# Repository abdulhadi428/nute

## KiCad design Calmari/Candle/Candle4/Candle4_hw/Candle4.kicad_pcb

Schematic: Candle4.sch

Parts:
ANT1: ANT_GENERAL
C1, C2, C3, C4, C12, C14, C17, C20: 0.1u
C5: 1u
C6, C8: 0.1u; CAP_0402
C7, C9: 10u; CAP_0402
C10, C11: 10pF; CAP_0402
C13, C18, C22: 220pF
C15, C16: 100pF; CAP_0402
C19, C21: 1pF; CAP_0402
C23: 1.8pF; CAP_0402
C24: 1.5pF; CAP_0402
D1: BAT54WS
DA1: NCP1400
DD1: STM32F100C4
DD2: CC2500
L1: 22uH
L2, L3, L4: 1.2nH; IND_0402
Q1: LED_RGB
R1: 30k; RES_0402
R2, R3, R4: 4k7; RES_0402
R5: 56k
R6, R7, R8: 51R; RES_0402
SW1, SW2, SW3: BUTTON
TP1, TP2: TESTPOINT
XL1: ST_SWD
XL2, XL3: CONN_1
XL4: CONN_2
XL5, XL6, XL7, XL8: CONN_3
XTAL1: 27MHz; 03225

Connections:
+3.3V: C1.1, C2.1, C3.1, C4.1, C5.1, C8.1, C9.1, C13.1, C14.1, C17.1, C18.1, C20.1, C22.1, D1.C, DA1.1 (CE), DA1.2 (OUT), DD1.1 (VBAT), DD1.9 (VDDA), DD1.24 (VDD1), DD1.36 (VDD2), DD1.48 (VDD3), DD2.4 (DVDD), DD2.9 (AVDD), DD2.11 (AVDD), DD2.14 (AVDD), DD2.15 (AVDD), DD2.18 (DGUARD), R2.2, R3.2, R4.2, XL1.1 (Vdd)
/Ant1: C15.1, DD2.12 (RF_P)
/Ant2: C16.1, DD2.13 (RF_N)
/BATT: C6.1, C7.1, L1.2, XL2.1
/BTN_DOWN: DD1.43 (PB7/SDA1/T17C1N), R3.1, SW2.2
/BTN_TX: DD1.11 (ADC1-1/T2C2/PA1), R4.1, SW3.2
/BTN_UP: DD1.42 (PB6/SCL1/T16C1N), R2.1, SW1.2
/CC_CS: DD1.13 (ADC1-3/T2C4/T15C2/RX2/PA3), DD2.7 (CSn)
/CC_GDO0: DD1.14 (ADC1-4/DAC1/CK2/PA4), DD2.6 (GDO0), TP2.1
/CC_MISO: DD1.16 (ADC1-6/T3C1/MISO1/PA6), DD2.2 (SO(GDO1))
/CC_MOSI: DD1.17 (ADC1-7/T3C2/MOSI1/PA7), DD2.20 (SI)
/CC_SCK: DD1.15 (ADC1-5/DAC2/SCK1/PA5), DD2.1 (SCLK)
/LED_B: DD1.40 ((PB4)/JTRST/(T3C1)), R8.1
/LED_G: DD1.19 (PB1/T3C4/ADC1-9), R7.1
/LED_R: DD1.18 (PB0/T3C3/ADC1-8), R6.1
/Lout: D1.A, DA1.5 (LX), L1.1
/SWCLK: DD1.37 (SWCLK/(JTCK)/(PA14)), XL1.2 (SWCLK)
/SWDIO: DD1.34 (SWDIO/(JTMS)/(PA13)), XL1.4 (SWDIO)
/WKUP: DD1.10 (ADC1-0/WKUP/PA0), R1.1, SW1.1, SW2.1, SW3.1
GND: ANT1.2 (GND), C1.2, C2.2, C3.2, C4.2, C5.2, C6.2, C7.2, C8.2, C9.2, C10.2, C11.2, C12.2, C13.2, C14.2, C17.2, C18.2, C19.2, C20.2, C22.2, C23.2, C24.2, DA1.4 (GND), DD1.8 (VSSA), DD1.23 (VSS1), DD1.35 (VSS2), DD1.44 (BOOT0), DD1.47 (VSS3), DD2.16 (GND), DD2.19 (GND), DD2.PAD (GND), L2.1, R1.2, R5.2, XL1.3 (GND), XL3.1, XL4.2 (PM), XL8.1, XL8.2 (PM), XL8.3, XTAL1.H
unnamed: C12.1, DD2.5 (DCOUPL)
unnamed: DD2.17 (RBIAS), R5.1
unnamed: DD1.30 (T1C2/TX1/PA9), XL4.1
unnamed: C21.2, C23.1, L3.1, L4.2
unnamed: Q1.BA, XL6.3
unnamed: Q1.RC, XL7.1
unnamed: Q1.BC (B), XL7.3
unnamed: Q1.GA, XL6.2 (PM)
unnamed: Q1.RA, XL6.1
unnamed: R7.2, XL5.2 (PM)
unnamed: R6.2, XL5.1
unnamed: R8.2, XL5.3
unnamed: Q1.GC (G), XL7.2 (PM)
unnamed: C16.2, C19.1, L3.2
unnamed: C15.2, C21.1, L2.2
unnamed: DD1.7 (NRST), TP1.1
unnamed: ANT1.1 (RF), C24.1, L4.1
unnamed: C11.1, DD2.10 (XOSC_Q2), XTAL1.2
unnamed: C10.1, DD2.8 (XOSC_Q1), XTAL1.1

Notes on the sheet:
Programming
Debug UART
Additional PCB
+BATTERY
-BATTERY

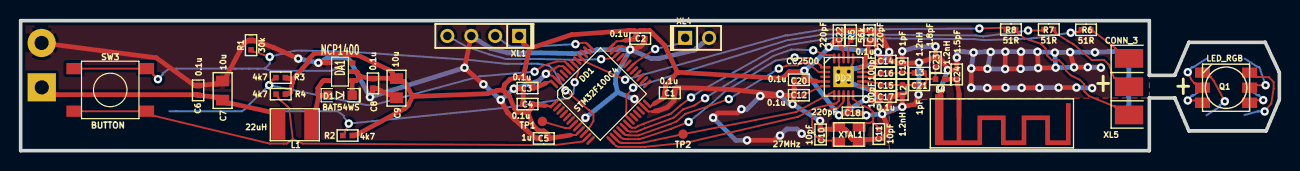
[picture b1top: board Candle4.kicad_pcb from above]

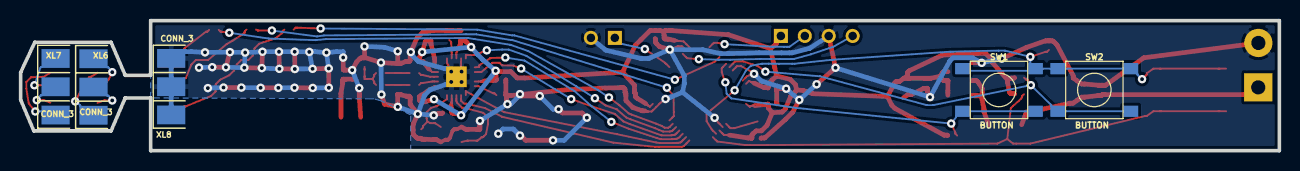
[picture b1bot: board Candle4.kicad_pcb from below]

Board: 2 copper layers, 133.6 x 13.8 mm, 56 parts (5 on the bottom side), 39 nets.

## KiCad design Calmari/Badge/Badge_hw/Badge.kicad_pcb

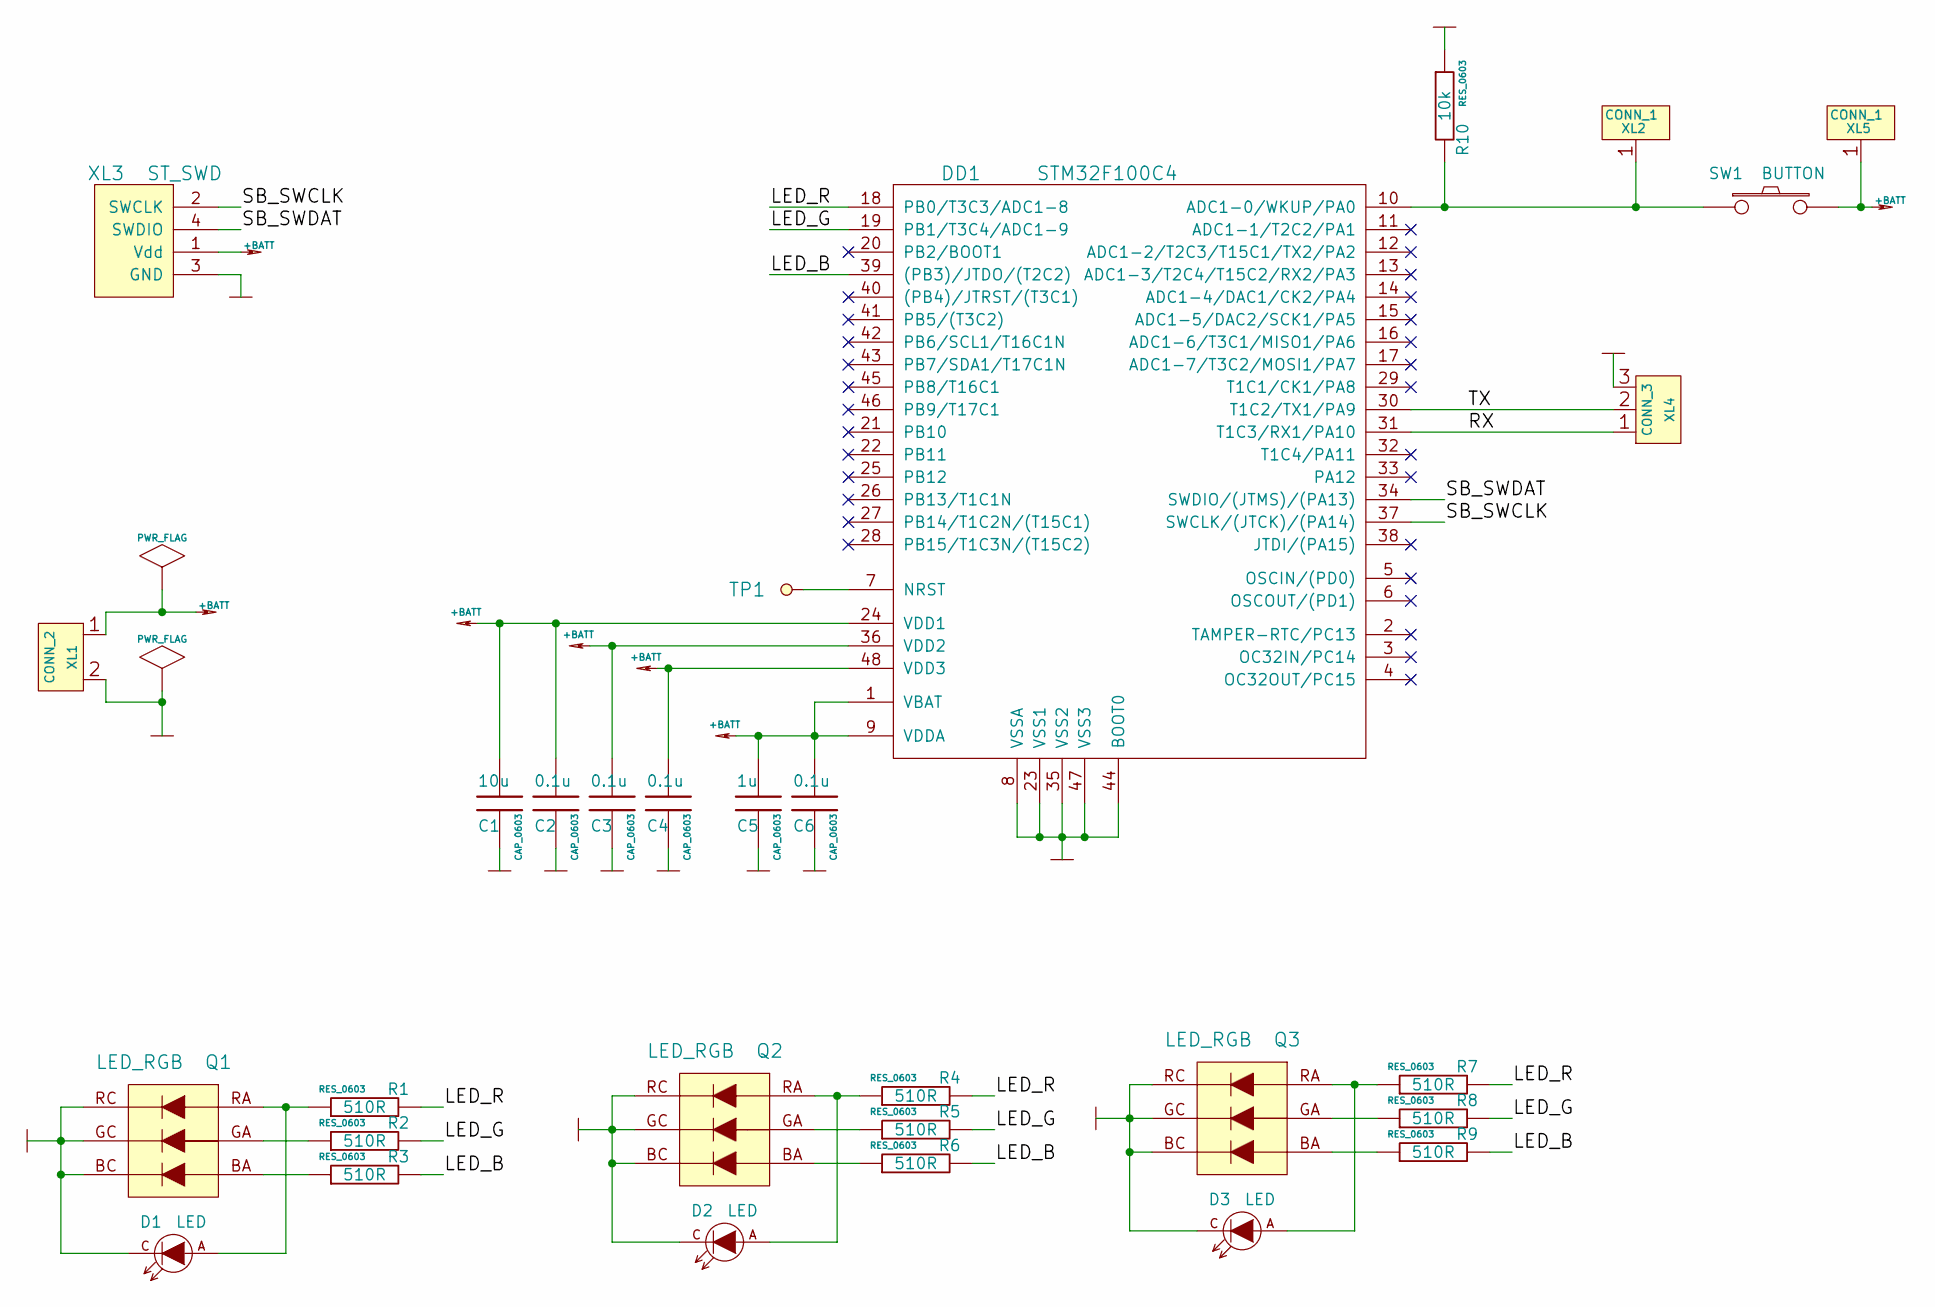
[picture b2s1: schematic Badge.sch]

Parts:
C1: 10u; CAP_0603
C2, C3, C4, C6: 0.1u; CAP_0603
C5: 1u; CAP_0603
D1, D2, D3: LED
DD1: STM32F100C4
Q1, Q2, Q3: LED_RGB
R1, R2, R3, R4, R5, R6, R7, R8, R9: 510R; RES_0603
R10: 10k; RES_0603
SW1: BUTTON
TP1: TESTPOINT
XL1: CONN_2
XL2, XL5: CONN_1
XL3: ST_SWD
XL4: CONN_3

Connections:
+BATT: C1.1, C2.1, C3.1, C4.1, C5.1, C6.1, DD1.1 (VBAT), DD1.9 (VDDA), DD1.24 (VDD1), DD1.36 (VDD2), DD1.48 (VDD3), SW1.2, XL1.1, XL3.1 (Vdd), XL5.1
/LED_B: DD1.39 ((PB3)/JTDO/(T2C2)), R3.2, R6.2, R9.2
/LED_G: DD1.19 (PB1/T3C4/ADC1-9), R2.2, R5.2, R8.2
/LED_R: DD1.18 (PB0/T3C3/ADC1-8), R1.2, R4.2, R7.2
/RX: DD1.31 (T1C3/RX1/PA10), XL4.1
/SB_SWCLK: DD1.37 (SWCLK/(JTCK)/(PA14)), XL3.2 (SWCLK)
/SB_SWDAT: DD1.34 (SWDIO/(JTMS)/(PA13)), XL3.4 (SWDIO)
/TX: DD1.30 (T1C2/TX1/PA9), XL4.2 (PM)
GND: C1.2, C2.2, C3.2, C4.2, C5.2, C6.2, D1.C, D2.C, D3.C, DD1.8 (VSSA), DD1.23 (VSS1), DD1.35 (VSS2), DD1.44 (BOOT0), DD1.47 (VSS3), Q1.BC (B), Q1.GC (G), Q1.RC, Q2.BC (B), Q2.GC (G), Q2.RC, Q3.BC (B), Q3.GC (G), Q3.RC, R10.1, XL1.2 (PM), XL3.3 (GND), XL4.3
unnamed: Q1.GA, R2.1
unnamed: Q1.BA, R3.1
unnamed: Q3.BA, R9.1
unnamed: Q2.BA, R6.1
unnamed: Q2.GA, R5.1
unnamed: D2.A, Q2.RA, R4.1
unnamed: D1.A, Q1.RA, R1.1
unnamed: D3.A, Q3.RA, R7.1
unnamed: Q3.GA, R8.1
unnamed: DD1.7 (NRST), TP1.1
unnamed: DD1.10 (ADC1-0/WKUP/PA0), R10.2, SW1.1, XL2.1

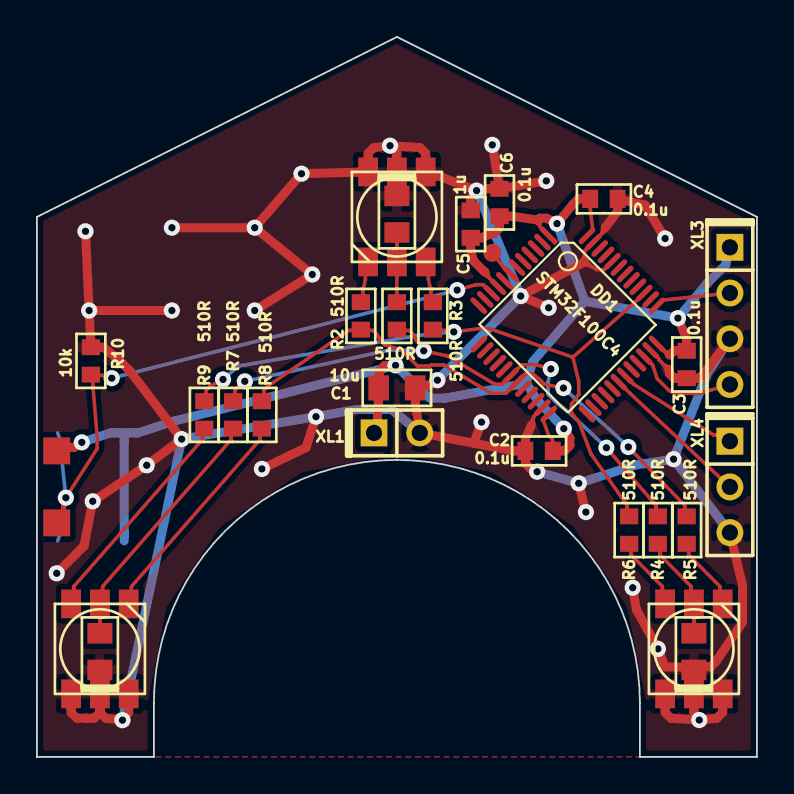
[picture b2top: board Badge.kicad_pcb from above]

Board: 2 copper layers, 40.0 x 40.0 mm, 30 parts (1 on the bottom side), 20 nets.

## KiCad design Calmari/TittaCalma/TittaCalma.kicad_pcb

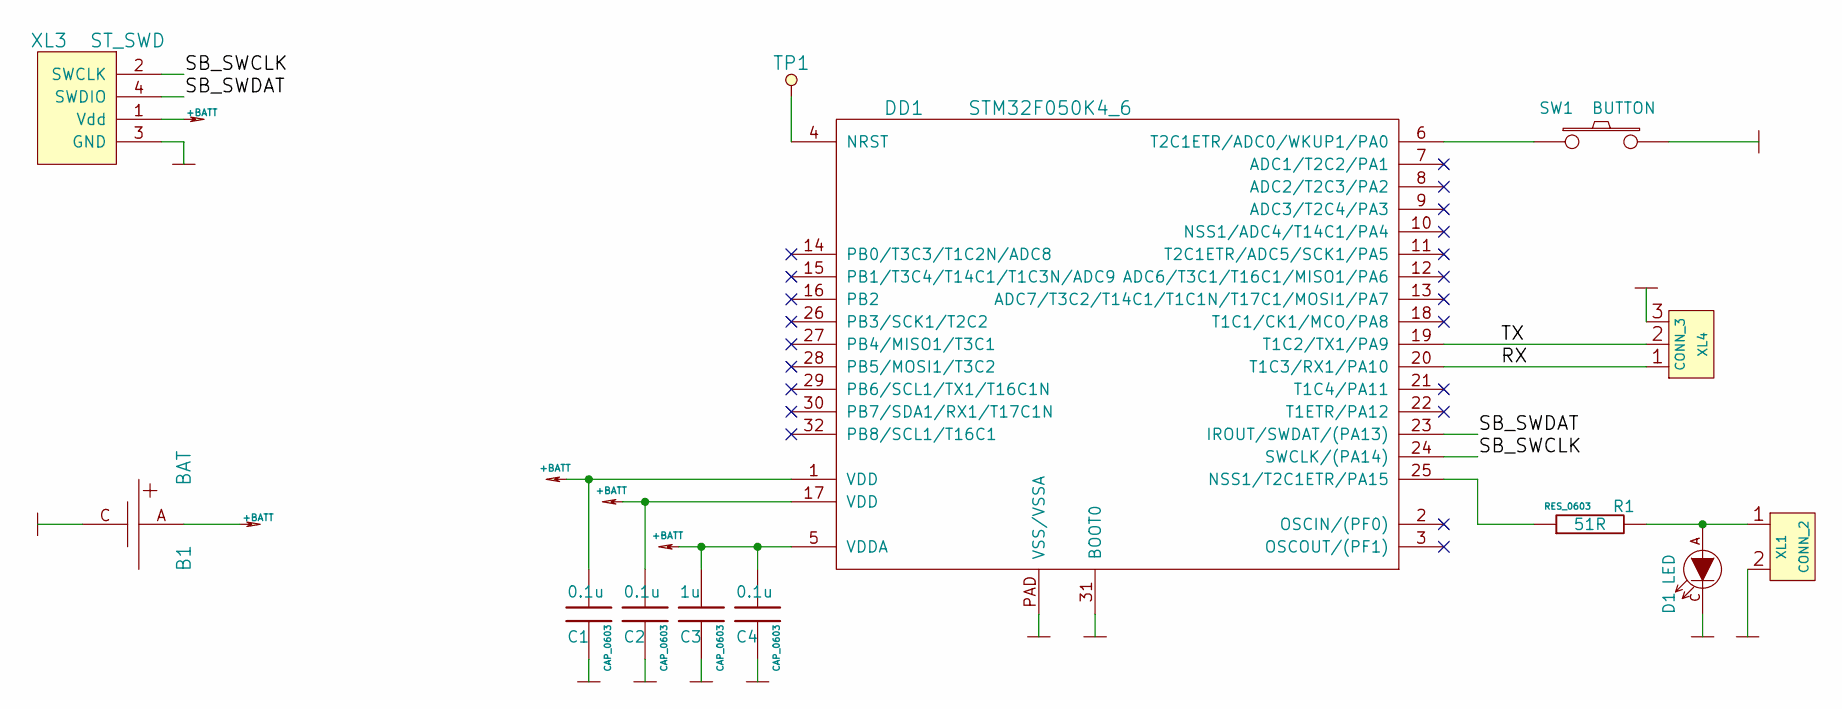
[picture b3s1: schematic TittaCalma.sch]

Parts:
B1: BAT
C1, C2, C4: 0.1u; CAP_0603
C3: 1u; CAP_0603
D1: LED
DD1: STM32F050K4_6
R1: 51R; RES_0603
SW1: BUTTON
TP1: TESTPOINT
XL1: CONN_2
XL3: ST_SWD
XL4: CONN_3

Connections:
+BATT: B1.A, C1.1, C2.1, C3.1, C4.1, DD1.1 (VDD), DD1.5 (VDDA), DD1.17 (VDD), XL3.1 (Vdd)
/RX: DD1.20 (T1C3/RX1/PA10), XL4.1
/SB_SWCLK: DD1.24 (SWCLK/(PA14)), XL3.2 (SWCLK)
/SB_SWDAT: DD1.23 (IROUT/SWDAT/(PA13)), XL3.4 (SWDIO)
/TX: DD1.19 (T1C2/TX1/PA9), XL4.2 (PM)
GND: B1.C, C1.2, C2.2, C3.2, C4.2, D1.C, DD1.31 (BOOT0), DD1.PAD (VSS/VSSA), SW1.2, XL1.2 (PM), XL3.3 (GND), XL4.3
unnamed: D1.A, R1.2, XL1.1
unnamed: DD1.6 (T2C1ETR/ADC0/WKUP1/PA0), SW1.1
unnamed: DD1.25 (NSS1/T2C1ETR/PA15), R1.1
unnamed: DD1.4 (NRST), TP1.1

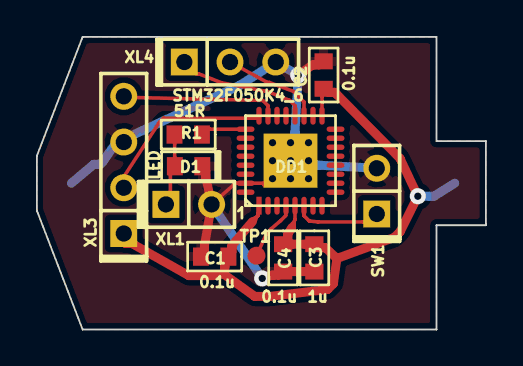
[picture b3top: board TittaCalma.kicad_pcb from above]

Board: 2 copper layers, 24.9 x 16.3 mm, 13 parts (1 on the bottom side), 10 nets.

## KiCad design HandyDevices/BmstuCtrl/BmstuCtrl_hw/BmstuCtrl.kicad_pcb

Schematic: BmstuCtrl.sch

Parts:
C1: 10u; CAP_0805
C2, C3, C5, C9, C10, C11, C12: 0.1u; CAP_0603
C4, C7, C8: 1u; CAP_0603
C6: 10n; CAP_0603
C13: 0.1u
D1, D2, D3, D4, D5: LED
D6, D7: BAT54SW
DA1: NCP583SQ
DA2: ADM3485
DA3, DA4, DA5, DA6: MC74VHC1
DD1: STM32L151CXTX
F1, F2: FUSE0R
HOLE1, HOLE2, HOLE3, HOLE4, HOLE5, HOLE6, HOLE7, HOLE9, HOLE10, HOLE11, HOLE12, HOLE13, HOLE14: HOLE_METALLED
R1: 100R; RES_0603
R2, R3, R4, R5: 1k; RES_0603
R6: 10k
R7: 10k; RES_0603
R8: 150R; RES_0603
U1: DLW21SN900SQ2
XL1: CONN_3
XL2: ST_SWD
XL3: CONN_4
XL4: CONN_3
XL5, XL6, XL7, XL8, XL10, XL11, XL12, XL13, XL14, XL15, XL16, XL17, XL18, XL19, XL20, XL21, XL22, XL23, XL24, XL25, XL26, XL27, XL28, XL29, XL30, XL31: CONN_GOST_1
XL9: DB9

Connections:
+3.3V: C1.1, C2.1, C3.1, C5.1, C6.1, C7.1, C8.1, C13.1, D6.2, D7.2, DA1.3 (Vout), DA2.8, DD1.1, DD1.9, DD1.24, DD1.36, DD1.48, XL2.1 (Vdd)
+5V: C4.1, C9.1, C10.1, C11.1, C12.1, DA1.1 (EN), DA1.4 (Vin), DA3.5 (Vcc), DA4.5 (Vcc), DA5.5 (Vcc), DA6.5 (Vcc), R7.1, XL7.1, XL10.1, XL15.1
/A: DA2.6, F1.2, U1.4
/B: DA2.7, F2.2, U1.1
/OutputEn: DA3.1 (~OE), DA4.1 (~OE), DA5.1 (~OE), DA6.1 (~OE), DD1.39, R7.2
/PATH2_1: DA3.4 (OutY), XL18.1
/PATH2_1_IN: DA3.2 (InA), DD1.40, R2.1
/PATH2_2: DA5.4 (OutY), XL26.1
/PATH2_2_IN: DA5.2 (InA), DD1.42, R4.1
/PATH3_1: DA4.4 (OutY), XL20.1
/PATH3_1_IN: DA4.2 (InA), DD1.41, R3.1
/PATH3_2: DA6.4 (OutY), XL28.1
/PATH3_2_IN: DA6.2 (InA), DD1.43, R5.1
/PWR_24V: XL5.1, XL16.1, XL24.1
/RS485_A: D6.3, F1.1, R8.1, U1.3, XL9.1
/RS485_B: D7.3, F2.1, R8.2, U1.2, XL9.2
/RX_I_TX_K: DD1.21, XL12.1
/SWCLK: DD1.37, XL2.2 (SWCLK)
/SWDIO: DD1.34, XL2.4 (SWDIO)
/TX_I_RX_K: DD1.22, XL13.1
/Tx_Rx: DA2.2, DA2.3, DD1.14, R6.1, XL4.2 (PM)
/UART2_RX: DA2.1, DD1.13, XL4.3
/UART2_TX: DA2.4, DD1.12, XL4.1
/UART_RX: DD1.31, XL1.3
/UART_TX: DD1.30, XL1.2 (PM)
GND: C1.2, C2.2, C3.2, C4.2, C5.2, C6.2, C7.2, C8.2, C9.2, C10.2, C11.2, C12.2, C13.2, D1.C, D2.C, D3.C, D4.C, D5.C, D6.1, D7.1, DA1.2 (GND), DA2.5, DA3.3 (GND), DA4.3 (GND), DA5.3 (GND), DA6.3 (GND), DD1.8, DD1.23, DD1.35, DD1.44, DD1.47, HOLE1.Hle, HOLE2.Hle, HOLE3.Hle, HOLE4.Hle, HOLE5.Hle, HOLE6.Hle, HOLE7.Hle, HOLE9.Hle, HOLE10.Hle, HOLE11.Hle, HOLE12.Hle, HOLE13.Hle, HOLE14.Hle, R6.2, XL1.1, XL2.3 (GND), XL3.4, XL6.1, XL8.1, XL9.5, XL9.H (SHLD), XL11.1, XL14.1, XL22.1, XL30.1
unnamed: DD1.2, XL3.3
unnamed: DD1.3, XL3.2 (PM)
unnamed: DD1.4, XL3.1
unnamed: DD1.18, R1.2
unnamed: D1.A, R1.1
unnamed: D4.A, R4.2
unnamed: D3.A, R3.2
unnamed: D5.A, R5.2
unnamed: D2.A, R2.2

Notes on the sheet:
Debug port
Programming
CPU
Power
Just Pins
3.3V 150mA power regulator
Shottki supress positive and negative peaks at signal fronts
Disable TX when start
RS-485
Imitator
Power input
To LNA
IND_COMM
IND2
IND3
Open_ALL_Paths
Switch1
Switch2
Output buffers Disabled by default
Holes
RS-485 interface
Power & Signal Connectors

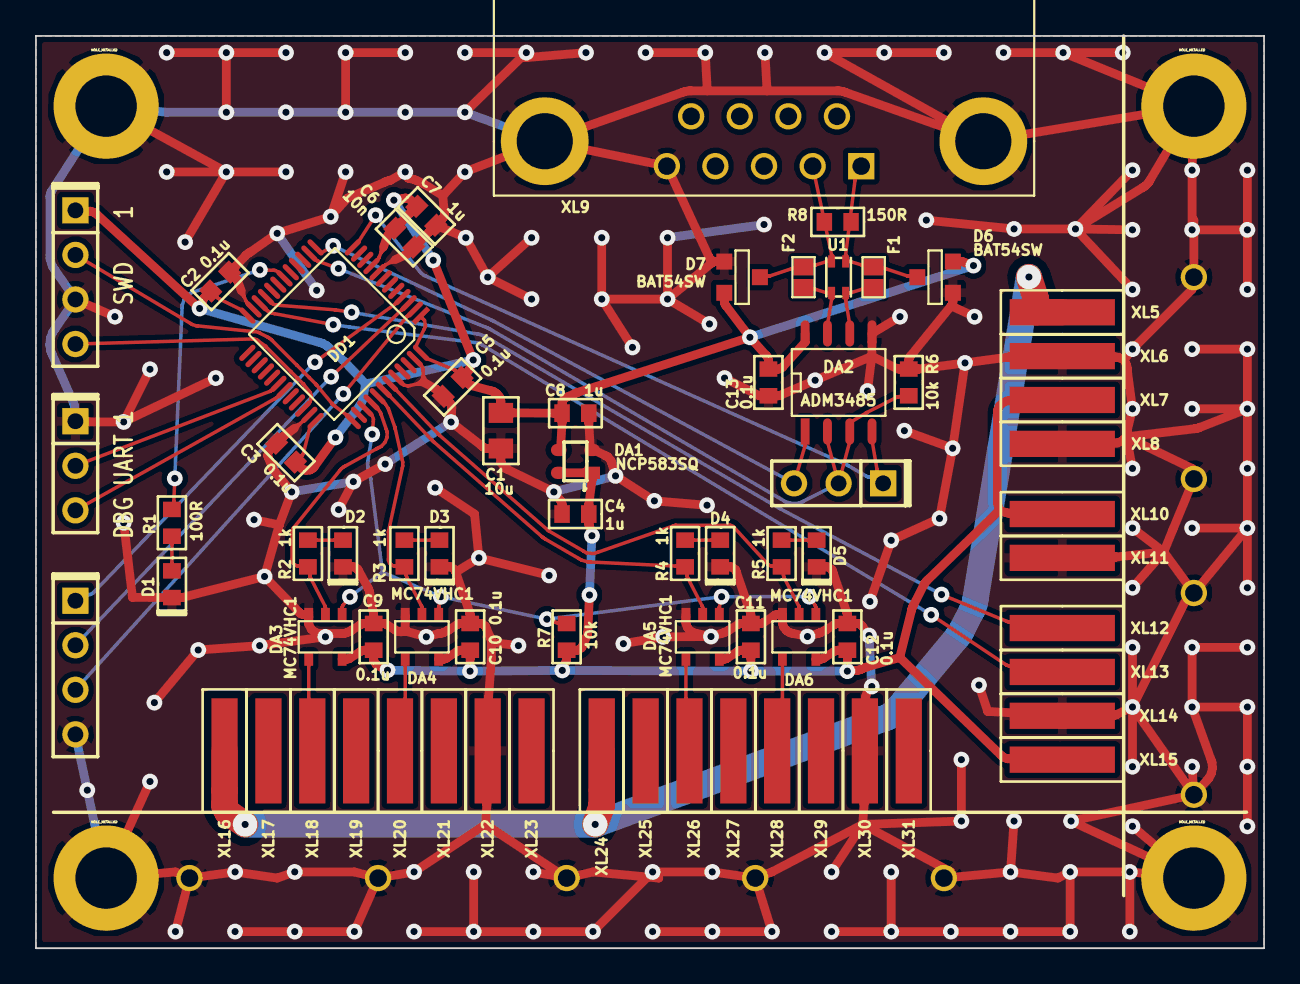
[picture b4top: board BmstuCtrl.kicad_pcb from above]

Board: 2 copper layers, 70.0 x 52.0 mm, 82 parts (0 on the bottom side), 35 nets.

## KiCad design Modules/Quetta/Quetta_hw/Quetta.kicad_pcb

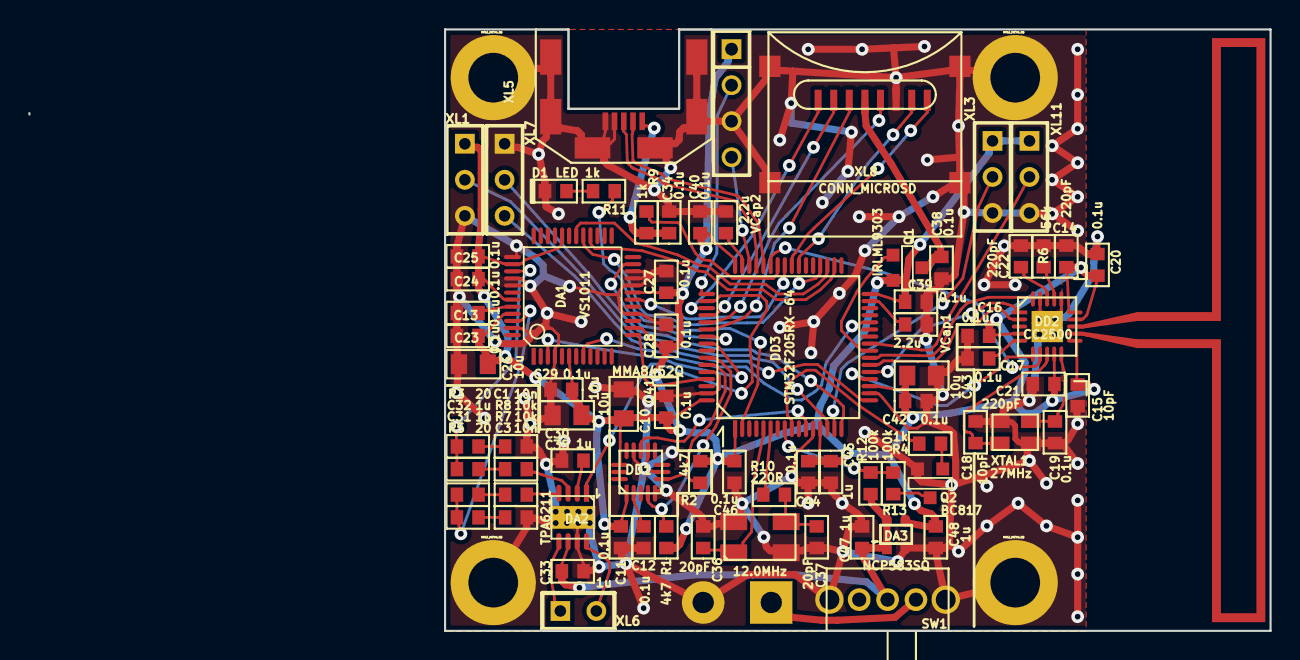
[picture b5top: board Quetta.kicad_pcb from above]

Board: 2 copper layers, 58.2 x 42.4 mm, 83 parts (0 on the bottom side), 71 nets.

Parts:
ANT1: ANT_PCB_NOCNTR; ANT_FOLDED_DIPOLE2
C1, C3: 10n; CAP_0603
C10, C26, C30, C43: 10u; CAP_0805
C11, C12, C13, C15, C16, C17, C20, C23, C24, C25, C27, C28, C29, C34, C38, C39, C40, C41, C42, C44, C46: 0.1u; CAP_0603
C14, C21, C22: 220pF; CAP_0603
C18, C19: 10pF; CAP_0603
C31, C32, C33, C35, C45, C47, C48: 1u; CAP_0603
C36, C37: 20pF; CAP_0603
D1: LED; LED0603
DA1: VS1011; LQFP48
DA2: TPA6211; DRB8
DA3: NCP583SQ; SC82AB
DD1: MMA8452Q; QFN16_5_3
DD2: CC2500; QFN20
DD3: STM32F205RX-64; LQFP64
HOLE1, HOLE2, HOLE3, HOLE4: HOLE_METALLED; Hole3_5_out6mm
Q1: IRLML9303; SOT23
Q2: BC817; SOT23
R1, R2: 4k7; RES_0603
R3, R5: 20; RES_0603
R4, R9, R11: 1k; RES_0603
R6: 56k; RES_0603
R7, R8: 10k; RES_0603
R10: 220R; RES_0603
R12, R13: 100k; RES_0603
SW1: SWITCH_H; SW_SK12D07VG
VCap1, VCap2: 2.2u; CAP_0603
XL1, XL3, XL7, XL11: CONN_3; SIL-3
XL4: ST_SWD; SIL-4
XL5: USB_MICRO_B; USBmicro_MOLEX_WM17142
XL6: CONN_2; SIL-2
XL8: CONN_MICROSD; MICROSD_CAP_FIX05A
XL9: CONN_1; SIL1_SQUARE_1MM5
XL10: CONN_1; SIL1_ROUND_1MM5
XTAL1: 27MHz; CRYSTAL_03225C4
XTAL2: 12.0MHz; CRYSTAL_0503x4-4

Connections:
+3.3V: C10.1, C11.1, C14.1, C15.1, C16.1, C20.1, C21.1, C23.1, C24.1, C25.1, C26.1, C27.1, C28.1, C29.1, C30.1, C39.1, C40.1, C41.1, C42.1, C43.1, C44.1, C45.1, C46.1, C48.1, DA1.6, DA1.14, DA1.19, DA1.32, DA1.38, DA1.43, DA1.45, DA3.3, DD1.1, DD1.14, DD2.4, DD2.9, DD2.11, DD2.14, DD2.15, DD3.1, DD3.13, DD3.19, DD3.32, DD3.48, DD3.64, Q1.2, R1.1, R2.2, XL1.1, XL3.1, XL4.1, XL11.1
+5V: C34.1, R9.2, XL5.1
+BATT: C33.1, C47.1, DA2.6, DA3.1, DA3.4, R12.1, SW1.2
/12MHz_Clk: DA1.18, DD3.41
/ACC_IRQ: DD1.11, DD3.11
/AMPLF_SHDN: DA2.1, DD3.50
/Ant1: ANT1.1, DD2.12
/Ant2: ANT1.2, DD2.13
/BATTERY_PLUS: SW1.3, XL9.1
/BAT_MEASURE: DD3.9, R4.1
/CC_CS: DD2.7, DD3.43
/CC_GDO0: DD2.6, DD3.20
/CC_MISO: DD2.2, DD3.22
/CC_MOSI: DD2.20, DD3.23
/CC_SCK: DD2.1, DD3.21
/I2C_SCL: DD1.4, DD3.58, R1.2
/I2C_SDA: DD1.6, DD3.59, R2.1
/RX2: DD3.17, XL7.3
/SD_CLK: DD3.53, XL8.5
/SD_CMD: DD3.54, XL8.3
/SD_DAT0: DD3.39, XL8.7
/SD_DAT1: DD3.40, XL8.8
/SD_DAT2: DD3.51, XL8.1
/SD_DAT3: DD3.52, XL8.2
/SD_POWER: DD3.24, Q1.1
/SD_VDD: C38.1, Q1.3, XL8.4
/SND_L: C31.2, DA1.46, R5.2
/SND_R: C32.2, DA1.39, R3.2
/SNS1_OUT: DD3.14, XL1.2
/SNS2_OUT: DD3.15, XL3.2
/SNS3_OUT: DD3.25, XL11.2
/SWCLK: DD3.49, XL4.2
/SWDIO: DD3.46, XL4.4
/TX2: DD3.16, XL7.2
/UBat_2: DD3.8, R12.2, R13.1
/USB_DM: DD3.44, XL5.2
/USB_DP: DD3.45, XL5.3
/VS_DREQ: DA1.8, DD3.28
/VS_RST: DA1.3, DD3.56
/VS_SCLK: DA1.28, DD3.34
/VS_SI: DA1.29, DD3.36
/VS_SO: DA1.30, DD3.35
/VS_XCS: DA1.23, DD3.55
/VS_XDCS: DA1.13, DD3.61
GND: C1.1, C3.1, C10.2, C11.2, C12.2, C13.2, C14.2, C15.2, C16.2, C17.2, C18.2, C19.2, C20.2, C21.2, C22.2, C23.2, C24.2, C25.2, C26.2, C27.2, C28.2, C29.2, C30.2, C33.2, C34.2, C35.2, C36.2, C37.2, C38.2, C39.2, C40.2, C41.2, C42.2, C43.2, C44.2, C45.2, C46.2, C47.2, C48.2, D1.C, DA1.4, DA1.16, DA1.20, DA1.21, DA1.22, DA1.37, DA1.40, DA1.41, DA1.47, DA2.7, DA2.PAD, DA3.2, DD1.5, DD1.7, DD1.10, DD1.12, DD2.16, DD2.19, DD2.PAD, DD3.12, DD3.18, DD3.60, DD3.63, HOLE1.Hle, HOLE2.Hle, HOLE3.Hle, HOLE4.Hle, Q2.2, R6.2, SW1.H, VCap1.2, VCap2.2, XL1.3, XL3.3, XL4.3, XL5.4, XL5.5, XL5.SHLD, XL7.1, XL8.6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
unnamed: C12.1, DD1.2
unnamed: DD3.47, VCap2.1
unnamed: C13.1, DA1.44
unnamed: DD2.17, R6.1
unnamed: C17.1, DD2.5
unnamed: C22.1, DD2.18
unnamed: C18.1, DD2.8, XTAL1.1
unnamed: C19.1, DD2.10, XTAL1.2
unnamed: C37.1, R10.2, XTAL2.2
unnamed: DD3.6, R10.1
unnamed: Q2.3, R13.2
unnamed: Q2.1, R4.2
unnamed: DD3.42, R9.1
unnamed: C32.1, R8.1
unnamed: DA2.4, R7.2
unnamed: DA2.8, XL6.2
unnamed: DA2.5, XL6.1
unnamed: DD3.31, VCap1.1
unnamed: DD3.2, R11.1
unnamed: C1.2, R3.1
unnamed: C3.2, R5.1
unnamed: C36.1, DD3.5, XTAL2.1
unnamed: C31.1, R7.1
unnamed: DA2.3, R8.2
unnamed: C35.1, DA2.2
unnamed: D1.A, R11.2

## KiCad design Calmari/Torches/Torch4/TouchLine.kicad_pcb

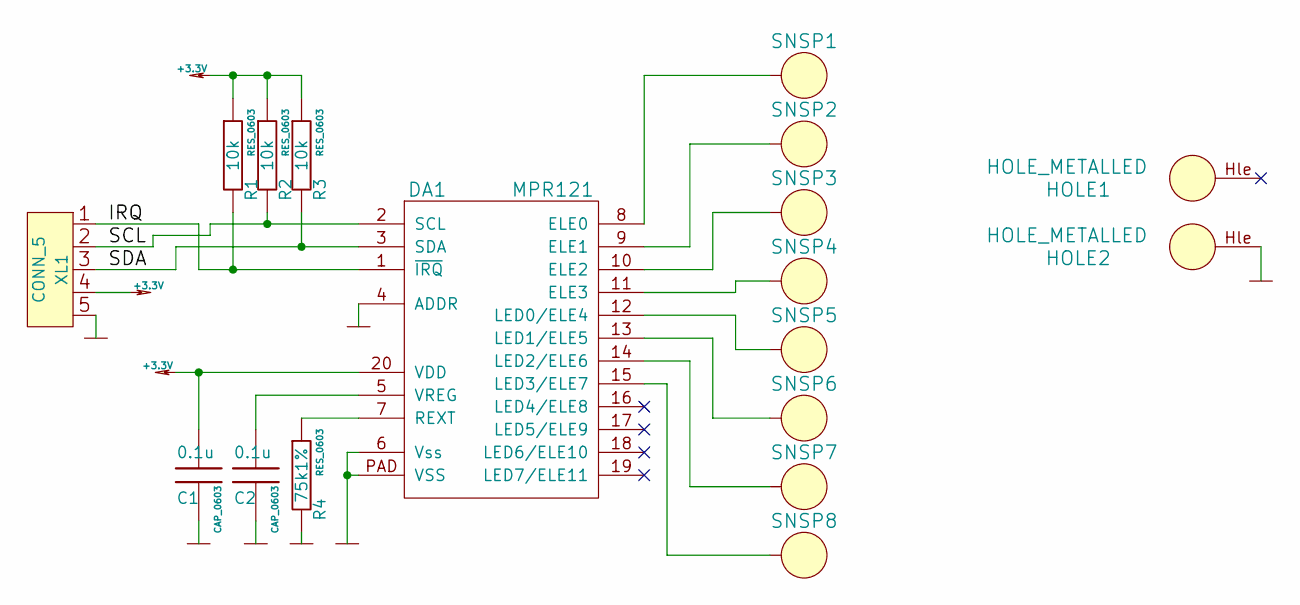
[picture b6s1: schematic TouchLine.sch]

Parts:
C1, C2: 0.1u; CAP_0603
DA1: MPR121
HOLE1, HOLE2: HOLE_METALLED
R1, R2, R3: 10k; RES_0603
R4: 75k1%; RES_0603
SNSP1, SNSP2, SNSP3, SNSP4, SNSP5, SNSP6, SNSP7, SNSP8: SENSORPAD
XL1: CONN_5

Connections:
+3.3V: C1.1, DA1.20 (VDD), R1.1, R2.1, R3.1, XL1.4
/IRQ: DA1.1 (~IRQ), R1.2, XL1.1
/SCL: DA1.2 (SCL), R2.2, XL1.2
/SDA: DA1.3 (SDA), R3.2, XL1.3
GND: C1.2, C2.2, DA1.4 (ADDR), DA1.6 (Vss), DA1.PAD (VSS), HOLE2.Hle, R4.2, XL1.5
unnamed: DA1.11 (ELE3), SNSP4.1
unnamed: DA1.12 (LED0/ELE4), SNSP5.1
unnamed: DA1.13 (LED1/ELE5), SNSP6.1
unnamed: DA1.14 (LED2/ELE6), SNSP7.1
unnamed: DA1.7 (REXT), R4.1
unnamed: C2.1, DA1.5 (VREG)
unnamed: DA1.9 (ELE1), SNSP2.1
unnamed: DA1.15 (LED3/ELE7), SNSP8.1
unnamed: DA1.10 (ELE2), SNSP3.1
unnamed: DA1.8 (ELE0), SNSP1.1

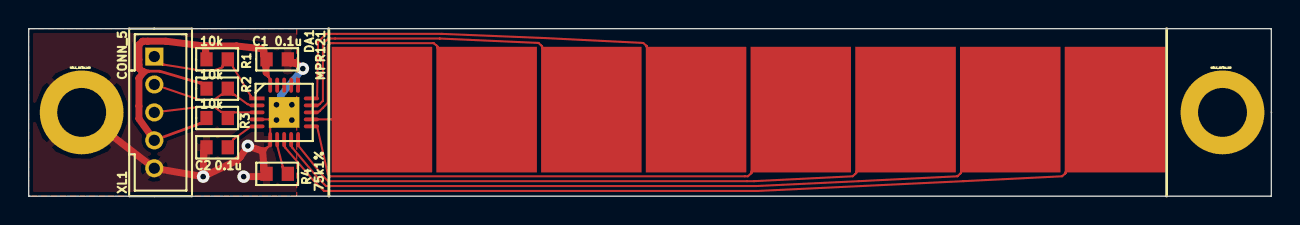
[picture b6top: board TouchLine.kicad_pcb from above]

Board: 2 copper layers, 89.0 x 12.0 mm, 18 parts (0 on the bottom side), 15 nets.

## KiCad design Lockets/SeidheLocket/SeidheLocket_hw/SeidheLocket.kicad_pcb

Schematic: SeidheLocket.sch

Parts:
ANT1: ANT_PCB_MONO
B3: BAT
BLN1: 0896BM15A0001
C1, C12: 10u; CAP_0603
C2: 1.8pF
C3, C8: 220pF
C4, C6: 10n
C5: 3.3pF
C7, C11, C21, C23: 0.1u
C9, C10: 10pF; CAP_0402
C13, C14, C18: 0.1u; CAP_0402
C15: 10n; CAP_0402
C16: 1u; CAP_0402
C22, C24: 10u
D1, D2: BAT54WS
DA1: NCP1400
DD1: STM32L151CXTX
DD2: CC1101
L1: 5.6nH; IND_0402
L2: 22uH
M1: MOTOR_PAD
Q1: MMBT2222
Q2: LED_RGB 5050
R1: 1k; RES_0402
R2: 56k
R3, R4, R5: 51R; RES_0603
R12: 1k
RP1, RP2: REFPOINT
SW1: BUTTON
TP1, TP2: TESTPOINT
XL1: ST_SWD
XL2: CONN_3
XL3: CONN_4
XTAL1: 27MHz; 03225

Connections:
+3.3V: C3.1, C4.1, C5.1, C6.1, C7.1, C8.1, C12.1, C13.1, C14.1, C15.1, C16.1, C18.1, C23.1, C24.1, D2.C, DA1.1 (CE), DA1.2 (OUT), DD1.1, DD1.9, DD1.24, DD1.36, DD1.48, DD2.4 (DVDD), DD2.9 (AVDD), DD2.11 (AVDD), DD2.14 (AVDD), DD2.15 (AVDD), DD2.18 (DGUARD), XL1.1 (Vdd)
+BATT: B3.A, C1.1, C21.1, C22.1, D1.C, L2.2, M1.2 (-), R1.2
/BLUE_LED: DD1.18, R5.1
/CC_CS: DD1.14, DD2.7 (CSn)
/CC_GDO0: DD1.13, DD2.6 (GDO0), TP1.1
/CC_GDO2: DD1.12, DD2.3 (GDO2), TP2.1
/CC_MISO: DD1.16, DD2.2 (SO(GDO1))
/CC_MOSI: DD1.17, DD2.20 (SI)
/CC_SCK: DD1.15, DD2.1 (SCLK)
/GREEN_LED: DD1.41, R4.1
/Lout: D2.A, DA1.5 (LX), L2.1
/RED_LED: DD1.19, R3.1
/RF1: BLN1.4 (Bal2), DD2.12 (RF_P)
/RF2: BLN1.3 (Bal1), DD2.13 (RF_N)
/SWCLK: DD1.37, XL1.2 (SWCLK)
/SWDIO: DD1.34, XL1.4 (SWDIO)
/UART_RX: DD1.31, XL2.3
/UART_TX: DD1.30, XL2.2 (PM)
/Vibro: DD1.42, R12.1
/VibroOut: D1.A, M1.1 (+), Q1.3 (C)
GND: B3.C, BLN1.2 (GND), BLN1.5 (GND), BLN1.6 (GND), C1.2, C2.2, C3.2, C4.2, C5.2, C6.2, C7.2, C8.2, C9.2, C10.2, C11.2, C12.2, C13.2, C14.2, C15.2, C16.2, C18.2, C21.2, C22.2, C23.2, C24.2, DA1.4 (GND), DD1.8, DD1.23, DD1.35, DD1.44, DD1.47, DD2.16 (GND), DD2.19 (GND), DD2.PAD (GND), M1.PAD (GND), Q1.2 (E), Q2.BC (B), Q2.GC (G), Q2.RC, R2.2, SW1.1, XL1.3 (GND), XL2.1, XL3.4, XTAL1.H
unnamed: ANT1.1, C2.1, L1.1
unnamed: DD1.22, XL3.2 (PM)
unnamed: DD1.25, XL3.3
unnamed: BLN1.1 (Unbal), L1.2
unnamed: DD1.45, SW1.2
unnamed: DD1.21, XL3.1
unnamed: DD1.10, R1.1
unnamed: DD2.17 (RBIAS), R2.1
unnamed: C11.1, DD2.5 (DCOUPL)
unnamed: Q2.BA, R5.2
unnamed: Q2.GA, R4.2
unnamed: Q2.RA, R3.2
unnamed: Q1.1 (B), R12.2
unnamed: C10.1, DD2.10 (XOSC_Q2), XTAL1.2
unnamed: C9.1, DD2.8 (XOSC_Q1), XTAL1.1

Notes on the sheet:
Debug port
Programming
CPU
Power
Radio
Matching circuit
L-07C5N6SV4
500R07S1R8BV4
1xAA
Just Pins
Indication

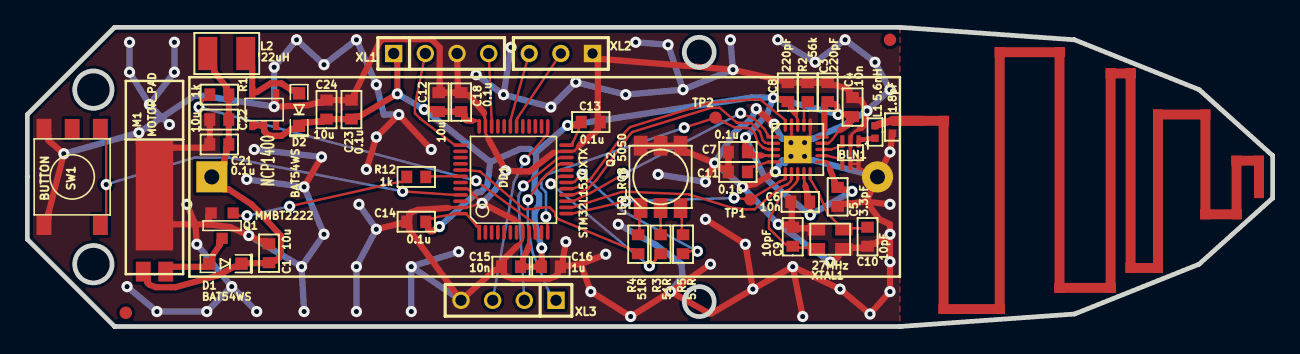
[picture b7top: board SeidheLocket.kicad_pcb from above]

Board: 2 copper layers, 99.9 x 24.0 mm, 49 parts (0 on the bottom side), 36 nets.

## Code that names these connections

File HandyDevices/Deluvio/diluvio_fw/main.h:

/*
 * File:   main.h
 * Author: Kreyl Laurelindo
 *
 * Created on 29 Íîÿáðü 2010 ã., 19:49
 */

#ifndef MAIN_H
#define	MAIN_H

#include "common.h"
#include <avr/io.h>
#include <stdbool.h>

// Power ok
#define PWROK_DDR   DDRA
#define PWROK_PORT  PORTA
#define PWROK_PIN   PINA
#define PWROK_P     PA3
#define POWER_OK()  bit_is_set(PWROK_PIN, PWROK_P)

// Pumps
#define PUMP_COUNT  4
#define PUMP_DDR    DDRA
#define PUMP_PORT   PORTA
#define PUMP1P      PA4
#define PUMP2P      PA5
#define PUMP3P      PA6
#define PUMP4P      PA7
// Max pump ON duration, s
#define PUMP_MAX_DURATION   252

// Water sensor
#define WATER_SNS_DDR    DDRA
#define WATER_SNS_PORT   PORTA
#define WATER_SNS_PIN    PINA
#define WATER_IN_P       PA1
#define WATER_R_P        PA0

#define WATER_IN_IS_HI() bit_is_set  (WATER_SNS_PIN, WATER_IN_P)
#define WATER_IN_IS_LO() bit_is_clear(WATER_SNS_PIN, WATER_IN_P)
#define WATER_R_LO()     WATER_SNS_PORT &= ~(1<<WATER_R_P)
#define WATER_R_HI()     WATER_SNS_PORT |=  (1<<WATER_R_P)

typedef enum {ModeDays, ModeHours} PumpPeriodMode_t;
typedef enum {PmpIdle, PmpMustPump, PmpBeeping, PmpPumping} PumpState_t;
typedef struct {
    bool Enabled;
    PumpPeriodMode_t PeriodMode;
    uint8_t Period;
    uint8_t PeriodLeft;
    uint8_t StartHour;
    uint8_t Duration;
    PumpState_t State;
    uint16_t Counter;
    uint8_t ID;
} pump_t;

extern pump_t Pumps[PUMP_COUNT];
extern bool IsPumping, PumpsSettingsChanged;

// ============================== Prototypes ===================================
void GeneralInit(void);

void PumpOn(uint8_t APump);
void PumpOffAll(void);
void Task_Pump(void);
void PumpsLoad(void);
void PumpsSave(void);

void CheckWater(void);
void CheckBattery(void);

void Task_Sleep(void);

#endif	/* MAIN_H */

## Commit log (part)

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2013-06-16 Event-driven, only one channel
2013-06-16 Tirusse2 release candidate
2013-06-16 Alfa-version. All features are working but some bugs are still possible
2013-06-17 Добавлена цветовая дифференциация добра и зла
2013-07-06 allow nullable controls on panel
2013-07-06 med staff
2013-07-06 minor synch
2013-07-06 minor icons
2013-07-06 OpenSpace fork
2013-07-06 DAC-based transmission works.
2013-07-07 price of honor
2013-07-07 deprecated old repositories
2013-07-07 remove
2013-07-07 exe-dll schema
2013-07-07 TF factory
2013-07-07 Timer-based generator added.
2013-07-07 move to vs10
2013-07-07 ITextStream.h
2013-07-07 TF factory 2
2013-07-08 new conv
2013-07-08 Panel factory changed
2013-07-08 removed useless trash
2013-07-10 led resistors change
2013-07-12 lume2 case added
2013-07-13 Calma04 added
2013-07-14 calma04 pcb added
2013-07-20 Candle3 btn evt processing in progress
2013-07-21 Radio works.
2013-07-23 Glove pre-revolution
2013-07-24 Angle-based measurements
2013-07-26 MINOR changes in ImageConvertor
2013-07-26 MINOR proper DllMain and generate debug info
2013-07-26 MINOR proper DllMain + tests + generate debug info
2013-07-26 MINOR merge with Krivda - updated to new ver
2013-07-26 images
2013-07-26 MINOR changes in API
2013-07-26 MINOR changes in visualizer
2013-07-26 MINOR to compile
2013-07-27 MAJOR Spec for app
2013-08-09 Indication changed, sleep allowed
2013-08-09 Demonstration of charge level at startup implemented
2013-08-10 Checked memory footprint, CPU time consumtion etc.
2013-08-12 After stats
2013-08-23 Girandole dome matrix & punch
2013-08-25 new stuff except armlet shell
2013-08-25 new krivda UI with factories, imagelists, pictureboxes
2013-08-28 Удален код настройки замков
2013-08-28 Убраны падения при невыбранном типе пилюль
2013-08-28 ShipStatus added. Including RanmaSubsystemStatus.cs
2013-08-29 Сделано сохранение и загрузка из файла кораблей
2013-08-29 PRICE OF HONOR 2 (Plan A:new UI), emulator only version in case of success will be merged with main development
2013-08-29 Перераспределены файлы по проектам, начат вопрос UI
2013-08-29 Добавлен параметр вероятности попадания
2013-08-29 Убраны остатки замеса про замки
2013-08-29 Добавлено сохранение комнат
2013-08-29 Добавлены взрывы комнат
2013-08-29 Добавил делегаты к классу корабля
2013-08-29 Удален старый UI взрыва отсеков
2013-08-29 Отображать имена отсеков в таблице
2013-08-29 Развернуть горизонтально контролы отсеков
2013-08-29 Окрасивлен GUI
2013-08-29 Добавлена функция взрыва случайного отсека и тестовая кнопка в нему.
2013-08-31 ChibiGate firmware completed.
2013-08-31 Большой update
2013-08-31 Удалил весь дублирующий код из {Lak/Big}Ship
    Теперь они отличаются ТОЛЬКО количеством плат и подсистем.
2013-08-31 Fixed bug with i2c; last byte dissapeared time after time.
2013-09-01 Проглатываем исключения при чтении пилюли
2013-09-01 Добавил таблицу значений и правильное значение для Ready
2013-09-01 Убрано сохранение кораблей и загрузка из профиля, теперь всегда грузим их из текущего каталога
2013-09-01 Дал название окну приложения
2013-09-01 Добавил IsOnline; Убрал ошибочный коммент с вопросом
2013-09-01 Теперь RanmaPlate работает поверх GateModel Статус online корабля отображается в GUI
2013-09-01 Fix bustage propertires/Annotations.cs
2013-09-01 Большая уборка, убраны ненужные референсы
2013-09-01 Поменял сообщение при поиске порта
2013-09-01 Предварительно переколбасил GUI
2013-09-01 Сделал чтение с таймаутом
2013-09-01 Добавил для теста корабль с одним гейтом
2013-09-01 Поправил номера гейтов и всякие мелочи в GUI
2013-09-01 Поправил ассерты, удалил лишниее
2013-09-01 Починили многопоточность в ShipControl
2013-09-01 Переодический апдейт состояния пилюли
2013-09-01 Added semaphore to UartPrintf. Count of gates increased to 9.
2013-09-01 Pill replaced
2013-09-01 Уменьшено количество паразитного трафика
2013-09-01 Обидный баг
2013-09-01 Показывать номер билда при запуске и в заголовке окна
2013-09-01 Добавил версию сервера в заголовок
2013-09-01 32 bytes instead of 16 (not ready version)
2013-09-01 Поправлен баг с падением треда записи
2013-09-02 Писать плату, даже если она ок.
2013-09-02 Сделан статус плат ремонта
2013-09-02 Рабочая версия обмена с Ранмой
2013-09-02 Обновлена таблица для легких повреждений
2013-09-02 Поправил таблицу Ранмы
2013-09-03 tortures
2013-09-03 removed
2013-09-03 removed temp, added thesis
2013-09-03 removed old tables
2013-09-03 Girandole release
2013-09-03 Добавлен вывод таймстампа
2013-09-03 krivda morning
2013-09-03 Выкинуть ненужные проверки и локи в демоне
2013-09-03 Форматирование температуры;
2013-09-03 Пересылать на браслет тип взрыва
2013-09-03 Добавлена сигнатура функций повреждения корабля
2013-09-03 Альфаверсия повреждения корабля
2013-09-03 Коннект к симулятору, кнопка в интерфейсы
2013-09-03 Static allocators added.
2013-09-03 Имена кораблей
2013-09-04 Добавлена TargetSeverity
2013-09-04 Allocators added for PriceOfHonor2
2013-09-04 Логика симулятора
2013-09-04 kl_allocator.h added
2013-09-04 Добавлено всякое
2013-09-04 template handlers
2013-09-04 img converter
2013-09-04 Minor bugs fixed: - system log shows on symptoms page - player name displayed with lag - recurcive messageboxes - explosion/messages now work
2013-09-05 added new time, sendappstate, impoved diagnostics
2013-09-05 GetTime & explosions
2013-09-05 gettime in h
2013-09-05 bugfixes, confirm msgbox
2013-09-05 med and minor signal dynamic
2013-09-05 prepare med interface
2013-09-05 KRIVDA FINISHED THAT FUCKING TRASH
2013-09-05 alpha version fixed persistent state, panacea restore and some more fixed update in case of armlet restart added test strings in logs
2013-09-05 30 sec PERIOD
2013-09-06 more space between room and clock
2013-09-06 minor fixes
2013-09-06 remove scrap
2013-09-06 medicine compiled after big refactoring blood is working
2013-09-06 i2c speed increased to 400kBit to work more reliable. Strange, but true.
2013-09-06 medicine beta many bugs or unimplemented side effects
2013-09-06 change out lustra/room behaviour
2013-09-06 pre-release
2013-09-06 newer version
2013-09-06 hacked version
2013-09-07 1.9.1
2013-09-11 Honor 2 changes
2013-09-14 More merges from PoH2
2013-09-15 Multiple changes. Just get all them
2013-09-16 Lots of changes to OS UI
2013-09-18 med forms UI done (except fro scroll)
2013-09-19 more UI
2013-09-22 Mushrooms added
2013-09-25 L15x kl_lib added
2013-10-17 Rf simulation added
2013-10-23 template f0 added
2013-10-23 os added
2013-10-29 Anganare project modified. Done: - LCD drawing position align center; - Time displayed in seconds; - LCD backlight PWM.
2013-10-29 Anganare project modified. Done: - Fixed bug with 0.0s time of load working.
2013-10-29 Anganare project modified. Done: - Increased speed of encoder reading; - Fixed bug with LCD axises initializing.
2013-10-29 Anganare project modified. Done: - Added load work indicating.
2013-11-01 Anganare project modified. Done: - Fixed bug manual load start when load is was started by time.
2013-11-08 Quetta added
2013-11-28 Anganare project modified. Done: - Change start mode to Time; - Change start time to 0.5 sec; - Fixed max time in Manual mode to 15 sec; - Remove Debug print info.
2013-12-11 BrainEnch PCB ready for production
2013-12-13 MotorControl2 Add: - PCB completed.
2013-12-14 quetta fsx added
2013-12-14 Template replaced with one with plugin v 1.0xxx
2013-12-22 Keys added
2013-12-22 +Key handlers
2013-12-22 Current and time setup implemented
2013-12-23 Current setup adjusted for R9 = 4.7k
2013-12-29 + ADC works ok, measuring battery voltage and current. Current not adjusted.
2013-12-30 + Battery mv2capacity added
2013-12-30 + Battery consts * L15x libs
2013-12-30 * LCD DrawImage fixed + icons.h. AlienDetector battery icons here.
2014-01-01 * CmdUart printf rewritten, direct vsprintf to buffer implemented + Current adс 2 uA implemented
2014-01-01 klprintf rewritten again
2014-01-01 LargeFonts printf implemented
2014-01-02 * DAC buf disabled * Current setup and measure constants adjusted
2014-01-02 * kl_printf bug fixed (wrong behavior printing %02u:%02u) + Timer implemented + On/Off indication with lightning icon
2014-01-04 + Overcurrent failure handling added + Qurtz-based timer implemented + Simulation circuits added
2014-01-04 + Sleep mode added, but not that effective: 10mA sleep, 22 active.
2014-01-04 + Iwdg-based sleep mode. Key check not implemented, though. Not useful, as in deep sleep consuption is over 7mA.
2014-01-04 + EEPROM storage of settings implemented
2014-01-04 * Lcd slightly changed: unused functions removed
2014-01-04 Crystal sch changed
2014-01-07 kl_lib updated to BrainEnch version
2014-01-24 + keys.cpp * libs moved to appropriate folders
2014-01-25 Avada2 firmware started. + Flash done
2014-01-25 + buzzer
2014-02-06 + Calma04
2014-02-06 * 5s delay after fire added
2014-02-06 + CmdUart, RX works
2014-02-06 + F10x libs
2014-02-06 + Added color saving to flash
2014-02-06 + ld section MyFlash added
2014-02-08 quetta radio fix
2014-02-09 * Dif pair * HiFreq
2014-02-18 firefly with flash save
2014-03-17 Mushroom_hw added
2014-03-18 NCP5007 added
2014-03-19 TPS61042 added
2014-03-21 Avada1,2 moved Avada3 added
2014-03-22 Avada3 pcb added
2014-03-23 LedPcb completed and added
2014-03-25 MotorControl3 Add.
2014-03-27 PCB completed
2014-04-05 + Firmware added: WS2812B LEDs work correctly
2014-04-05 * Timer constructor removed, added to init
2014-04-09 Deleted ISO IC's.
2014-04-10 Avada3 firmware release candidate
2014-04-10 + Color Modes added: simultaneously or one by one
2014-04-10 + radio + application.cpp * Events enabled * CPU freq lowered to 4MHz * WS2812 rewritten to fit frequency
2014-04-11 * Sch ready
2014-04-14 + Footprint assigned to components. Check values and e.t.c.
2014-04-15 kl_lib_f100 renew
2014-04-16 * USB connector replaced with B type
2014-04-19 + PCB
2014-04-23 Files to upgrade firmware by cmd file.
2014-04-30 Proceeding
2014-05-01 Schematic seems completed (again)
2014-05-30 MotorControl3 Footprint aligned.
2014-05-30 MotorCtrl3 start to trace board.
2014-07-21 + SeidheLocket
2014-07-29 * SeidheLocket final PCB + GERBER
2014-08-17 + AccBall One led only
2014-08-17 + 4 LEDs simultaneously
2014-09-23 + Torch4Fw
2014-09-24 * MPR touches detected successfully
2014-09-25 * Coord calculated
2014-09-25 * Settings updated: 34 samples, not 6
2014-09-27 Touch made event driving. Dx implemented. Filter exists, but commented out.
2014-10-21 + cmd works
2014-10-21 + hex * infinite cycle broken
2014-10-22 * Fixed "Old goto" bug
2014-10-29 + Quetta Gerber + Quetta Portrait, speaking
2014-10-30 Release candidate + cfg read + random phrase speak
2014-11-23 + GondorLocket/Stone
2014-12-01 + BmstuCtrl
2014-12-01 * Sch seems completed
2014-12-11 Gerber ready
2014-12-15 TittaCalma add
2014-12-15 zones updated
2014-12-19 + Tittacalma fw
2014-12-21 * small improvement of getlines
2014-12-21 + button * Fixed chsyslock in FadeIn/FadeOut
2014-12-24 * Sleep mode fixed
2015-01-08 + LockNFC3
2015-01-09 + LedRGB blinker ok
2015-01-10 proceeding with PN
2015-01-11 + PN data exchange works
2015-01-11 + IDStore added Proceeding
2015-01-11 + Keys interface works ok
2015-01-11 + IdStore add and remove
2015-01-16 + RGB Leds work
2015-01-17 + universal simple sensors module * Keys edited to work with the module
2015-01-18 + Sound works * Main thread sz increased to 4096 Bytes
2015-01-18 + speaks when card appeared etc.
2015-01-18 + SndList. It works. Something bad with mp3 playback.
2015-01-21 * Fixed bug with wav playing.
2015-01-25 + proceeding with ID Store save * Fixed bug with sensor connection to button instead of USB
2015-01-30 + Badge hw and fw (including button)
2015-01-31 + Four groups implemented + Adder/remover + indication in progress
2015-02-01 * Filesystem settings changed to allow reentrance * SD card speed lowered to make it work robust when power is battery * Sound delays changed to make it work at low frequency * Group names changed + 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
2015-02-08 + WhatNext + Pictures' PDF + shortPress starts/stops color changing
2015-02-08 + State & color saving/loading * long press: on/off * short press: start/stop color changing
2015-02-24 * Capacitors values added
2015-03-03 Candle4 pcb added
2015-03-05 Candle4 fsproj added
